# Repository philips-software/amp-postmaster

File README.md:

# Postmaster (Programmer Of ST Microcontrollers Attached to ST Experiment boaRds)

<!-- markdownlint-disable -->

<!-- markdownlint enable -->

## Overview

Postmaster is a device that clicks on top of an STM32 Nucleo-F767ZI board from ST Microelectronics, and through its Ethernet connector you can program the Nucleo and communicate with it.

In this way, Postmaster is usable in hardware-in-the-loop tests, where a test board is reachable through the internet. That test board can first be programmed with the correct firmware. For communicating with the test board, a client can connect to Postmaster via a websocket connection, and talk to the attached board either via a plain UART connection, or via an [ECHO](https://philips-software.github.io/amp-embedded-infra-lib/embedded_infrastructure_library/7.0.0/Echo.html) connection. This communication line is used to execute tests.

Test boards enabled by Postmaster are intended to be inherently scalable; Adding tests boards in a setup should be as simple as putting a Postmaster on top of it, configuring the Postmaster with a few labels describing the characteristics of that board, and connecting it to the internet. A locally installed proxy (also part of this archive) provides discoverability of all Postmasters in its vicinity, and routes incoming requests for boards with certain characteristics to any available board.

By providing a schematics and PCB layout, the Postmaster firmware, and various tools, this repository aims to provide a full suite of components tackling all aspects of connecting a hardware-in-the-loop test board to the cloud.

Requirements of Postmaster are documented [here](Documents/Requirements.md).

## Community

This project uses the [CODE_OF_CONDUCT](./CODE_OF_CONDUCT.md) to define expected conduct in our community. Instances of abusive, harassing, or otherwise unacceptable behavior may be reported by contacting a project [CODEOWNER](.github/CODEOWNERS)

## Changelog

See [CHANGELOG](./CHANGELOG.md) for more info on what's been changed.

## Build

The Postmaster binaries can be built by executing the following commands:

```shell
cmake --preset stm32f407
cmake --build --preset stm32f407-MinSizeRel
```

The postmaster.flex utility can be build by executing the following commands:

```shell
cmake --preset host
cmake --build --preset host-RelWithDebInfo
```

## Reporting vulnerabilities

If you find a vulnerability, please report it to us!
See [security](.github/SECURITY.md) for more information.

## Licenses

See [LICENSE](./LICENSE.md)

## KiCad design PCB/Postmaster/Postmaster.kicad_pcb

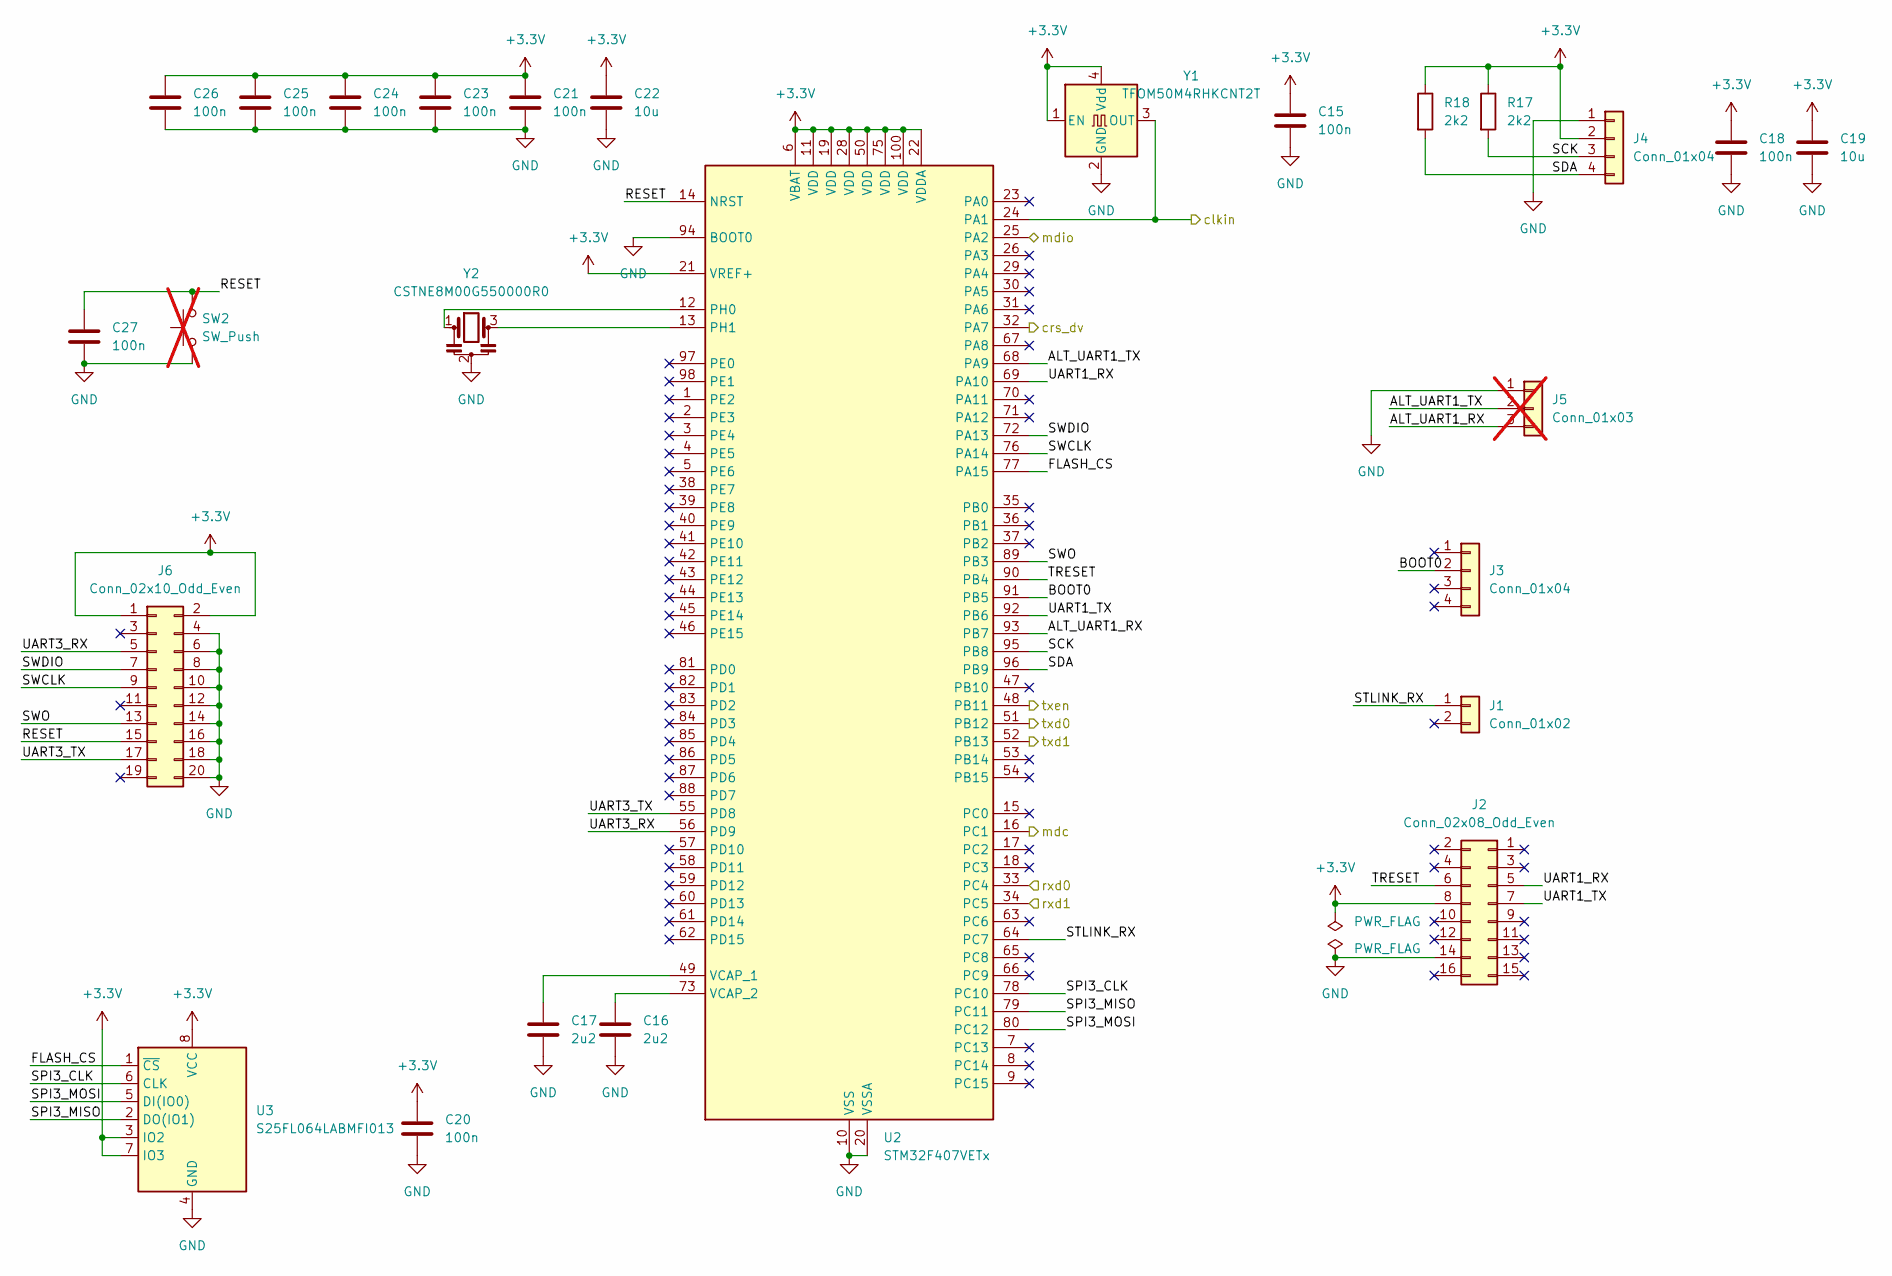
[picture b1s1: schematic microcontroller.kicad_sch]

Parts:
C15, C18, C20, C21, C23, C24, C25, C26, C27: 100n; C_0603_1608Metric; JLCPCBPart C14663
C16, C17: 2u2; C_0603_1608Metric; JLCPCBPart C23630
C19, C22: 10u; C_0603_1608Metric; JLCPCBPart C19702
J1: Conn_01x02; PinSocket_1x02_P2.54mm_Vertical; JLCPCBPart C7509512
J2: Conn_02x08_Odd_Even; PinHeader_2x08_P2.54mm_Vertical; JLCPCBPart C5383108
J3, J4: Conn_01x04; PinHeader_1x04_P2.54mm_Vertical; JLCPCBPart C7430360
J5: Conn_01x03; PinHeader_1x03_P2.54mm_Vertical; not fitted
J6: Conn_02x10_Odd_Even; IDC-Header_2x10_P2.54mm_Vertical; JLCPCBPart C3405
R17, R18: 2k2; R_0603_1608Metric; JLCPCBPart C4190
SW2: SW_Push; SW_SPST_TL3305B; not fitted
U2: STM32F407VETx; LQFP-100_14x14mm_P0.5mm; JLCPCBPart C28730
U3: S25FL064LABMFI013; SOIC-8_5.23x5.23mm_P1.27mm; JLCPCBPart C2951282
Y1: TFOM50M4RHKCNT2T; Oscillator_SMD_Abracon_ASE-4Pin_3.2x2.5mm; JLCPCBPart C454615
Y2: CSTNE8M00G550000R0; Resonator_SMD_Murata_CSTxExxV-3Pin_3.0x1.1mm; JLCPCBPart C341522

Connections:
+3.3V: C15.1, C18.1, C19.1, C20.1, C21.1, C22.1, C23.1, C24.1, C25.1, C26.1, J2.8, J4.2, J6.1, J6.2, R17.1, R18.1, U2.6 (VBAT), U2.11 (VDD), U2.19 (VDD), U2.21 (VREF+), U2.22 (VDDA), U2.28 (VDD), U2.50 (VDD), U2.75 (VDD), U2.100 (VDD), U3.3 (IO2), U3.7 (IO3), U3.8 (VCC), Y1.1 (EN), Y1.4 (Vdd); also elsewhere on the board
/Ethernet/clkin: U2.24 (PA1), Y1.3 (OUT); also elsewhere on the board
/Ethernet/crs_dv: U2.32 (PA7); also elsewhere on the board
/Ethernet/mdc: U2.16 (PC1); also elsewhere on the board
/Ethernet/mdio: U2.25 (PA2); also elsewhere on the board
/Ethernet/rxd0: U2.33 (PC4); also elsewhere on the board
/Ethernet/rxd1: U2.34 (PC5); also elsewhere on the board
/Ethernet/txd0: U2.51 (PB12); also elsewhere on the board
/Ethernet/txd1: U2.52 (PB13); also elsewhere on the board
/Ethernet/txen: U2.48 (PB11); also elsewhere on the board
/Microcontroller/ALT_UART1_RX: J5.3, U2.93 (PB7)
/Microcontroller/ALT_UART1_TX: J5.2, U2.68 (PA9)
/Microcontroller/BOOT0: J3.2, U2.91 (PB5)
/Microcontroller/FLASH_CS: U2.77 (PA15), U3.1 (~CS)
/Microcontroller/RESET: C27.1, J6.15, SW2.2, U2.14 (NRST)
/Microcontroller/SCK: J4.3, R17.2, U2.95 (PB8)
/Microcontroller/SDA: J4.4, R18.2, U2.96 (PB9)
/Microcontroller/SPI3_CLK: U2.78 (PC10), U3.6 (CLK)
/Microcontroller/SPI3_MISO: U2.79 (PC11), U3.2 (DO(IO1))
/Microcontroller/SPI3_MOSI: U2.80 (PC12), U3.5 (DI(IO0))
/Microcontroller/STLINK_RX: J1.1, U2.64 (PC7)
/Microcontroller/SWCLK: J6.9, U2.76 (PA14)
/Microcontroller/SWDIO: J6.7, U2.72 (PA13)
/Microcontroller/SWO: J6.13, U2.89 (PB3)
/Microcontroller/TRESET: J2.6, U2.90 (PB4)
/Microcontroller/UART1_RX: J2.5, U2.69 (PA10)
/Microcontroller/UART1_TX: J2.7, U2.92 (PB6)
/Microcontroller/UART3_RX: J6.5, U2.56 (PD9)
/Microcontroller/UART3_TX: J6.17, U2.55 (PD8)
GND: C15.2, C16.2, C17.2, C18.2, C19.2, C20.2, C21.2, C22.2, C23.2, C24.2, C25.2, C26.2, C27.2, J2.14, J4.1, J5.1, J6.4, J6.6, J6.8, J6.10, J6.12, J6.14, J6.16, J6.18, J6.20, SW2.1, U2.10 (VSS), U2.20 (VSSA), U2.27 (VSS), U2.74 (VSS), U2.94 (BOOT0), U2.99 (VSS), U3.4 (GND), Y1.2 (GND), Y2.2; also elsewhere on the board
unnamed: U2.12 (PH0), Y2.1
unnamed: U2.13 (PH1), Y2.3
unnamed: C17.1, U2.49 (VCAP_1)
unnamed: C16.1, U2.73 (VCAP_2)

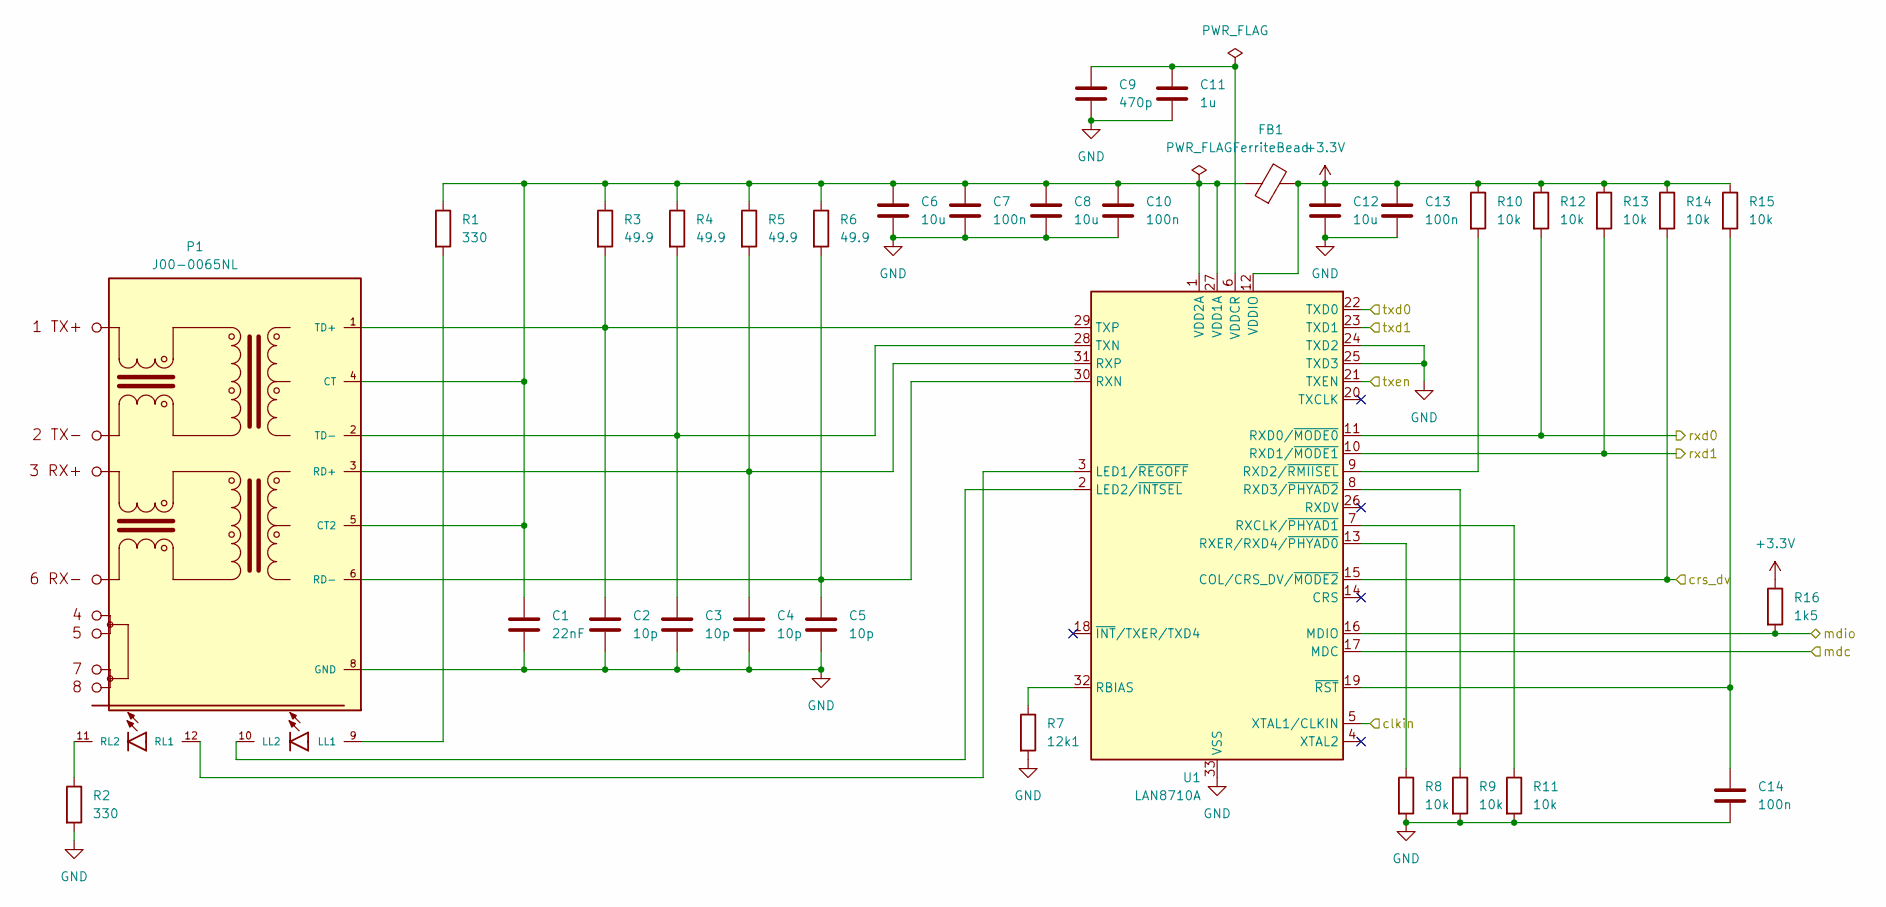
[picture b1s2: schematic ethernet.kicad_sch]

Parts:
C1: 22nF; C_0603_1608Metric; JLCPCBPart C21122
C2, C3, C4, C5: 10p; C_0603_1608Metric; JLCPCBPart C1634
C6, C8, C12: 10u; C_0603_1608Metric; JLCPCBPart C19702
C7, C10, C13, C14: 100n; C_0603_1608Metric; JLCPCBPart C14663
C9: 470p; C_0603_1608Metric; JLCPCBPart C1620
C11: 1u; C_0805_2012Metric; JLCPCBPart C15849
FB1: FerriteBead; L_0603_1608Metric; JLCPCBPart C1002
P1: J00-0065NL; PULSE_J00-0065NL; JLCPCBPart C3178480
R1, R2: 330; R_0603_1608Metric; JLCPCBPart C23138
R3, R4, R5, R6: 49.9; R_0603_1608Metric; JLCPCBPart C269902
R7: 12k1; R_0603_1608Metric; JLCPCBPart C22864
R8, R9, R10, R11, R12, R13, R14, R15: 10k; R_0603_1608Metric; JLCPCBPart C25804
R16: 1k5; R_0603_1608Metric; JLCPCBPart C22843
U1: LAN8710A; QFN-32-1EP_5x5mm_P0.5mm_EP3.3x3.3mm_ThermalVias; JLCPCBPart C46185

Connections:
+3.3V: C12.1, C13.1, FB1.2, R10.1, R12.1, R13.1, R14.1, R15.1, R16.1, U1.12 (VDDIO); also elsewhere on the board
/Ethernet/clkin: U1.5 (XTAL1/CLKIN); also elsewhere on the board
/Ethernet/crs_dv: R14.2, U1.15 (COL/CRS_DV/~MODE2); also elsewhere on the board
/Ethernet/mdc: U1.17 (MDC); also elsewhere on the board
/Ethernet/mdio: R16.2, U1.16 (MDIO); also elsewhere on the board
/Ethernet/rxd0: R12.2, U1.11 (RXD0/~MODE0); also elsewhere on the board
/Ethernet/rxd1: R13.2, U1.10 (RXD1/~MODE1); also elsewhere on the board
/Ethernet/txd0: U1.22 (TXD0); also elsewhere on the board
/Ethernet/txd1: U1.23 (TXD1); also elsewhere on the board
/Ethernet/txen: U1.21 (TXEN); also elsewhere on the board
GND: C1.2, C2.2, C3.2, C4.2, C5.2, C6.2, C7.2, C8.2, C9.2, C10.2, C11.2, C12.2, C13.2, C14.2, P1.8 (GND), R2.2, R7.2, R8.2, R9.2, R11.2, U1.24 (TXD2), U1.25 (TXD3), U1.33 (VSS); also elsewhere on the board
unnamed: C1.1, C6.1, C7.1, C8.1, C10.1, FB1.1, P1.4 (CT), P1.5 (CT2), R1.1, R3.1, R4.1, R5.1, R6.1, U1.1 (VDD2A), U1.27 (VDD1A)
unnamed: P1.9 (LL1), R1.2
unnamed: P1.10 (LL2), U1.2 (LED2/~INTSEL)
unnamed: C4.1, P1.3 (RD+), R5.2, U1.31 (RXP)
unnamed: C5.1, P1.6 (RD-), R6.2, U1.30 (RXN)
unnamed: P1.12 (RL1), U1.3 (LED1/~REGOFF)
unnamed: P1.11 (RL2), R2.1
unnamed: C2.1, P1.1 (TD+), R3.2, U1.29 (TXP)
unnamed: C3.1, P1.2 (TD-), R4.2, U1.28 (TXN)
unnamed: R7.1, U1.32 (RBIAS)
unnamed: R11.1, U1.7 (RXCLK/~PHYAD1)
unnamed: R10.2, U1.9 (RXD2/~RMIISEL)
unnamed: R9.1, U1.8 (RXD3/~PHYAD2)
unnamed: R8.1, U1.13 (RXER/RXD4/~PHYAD0)
unnamed: C9.1, C11.1, U1.6 (VDDCR)
unnamed: C14.1, R15.2, U1.19 (~RST)

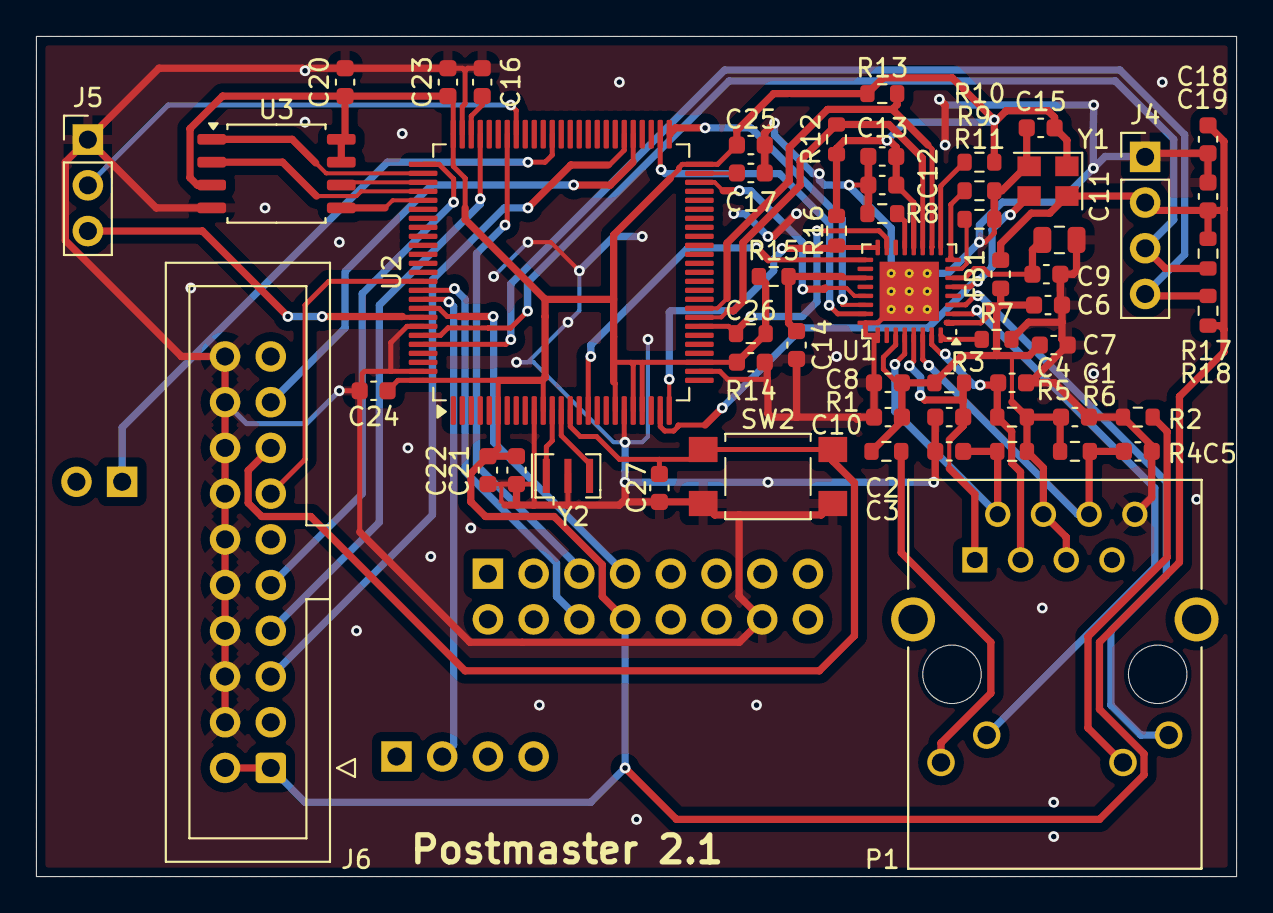
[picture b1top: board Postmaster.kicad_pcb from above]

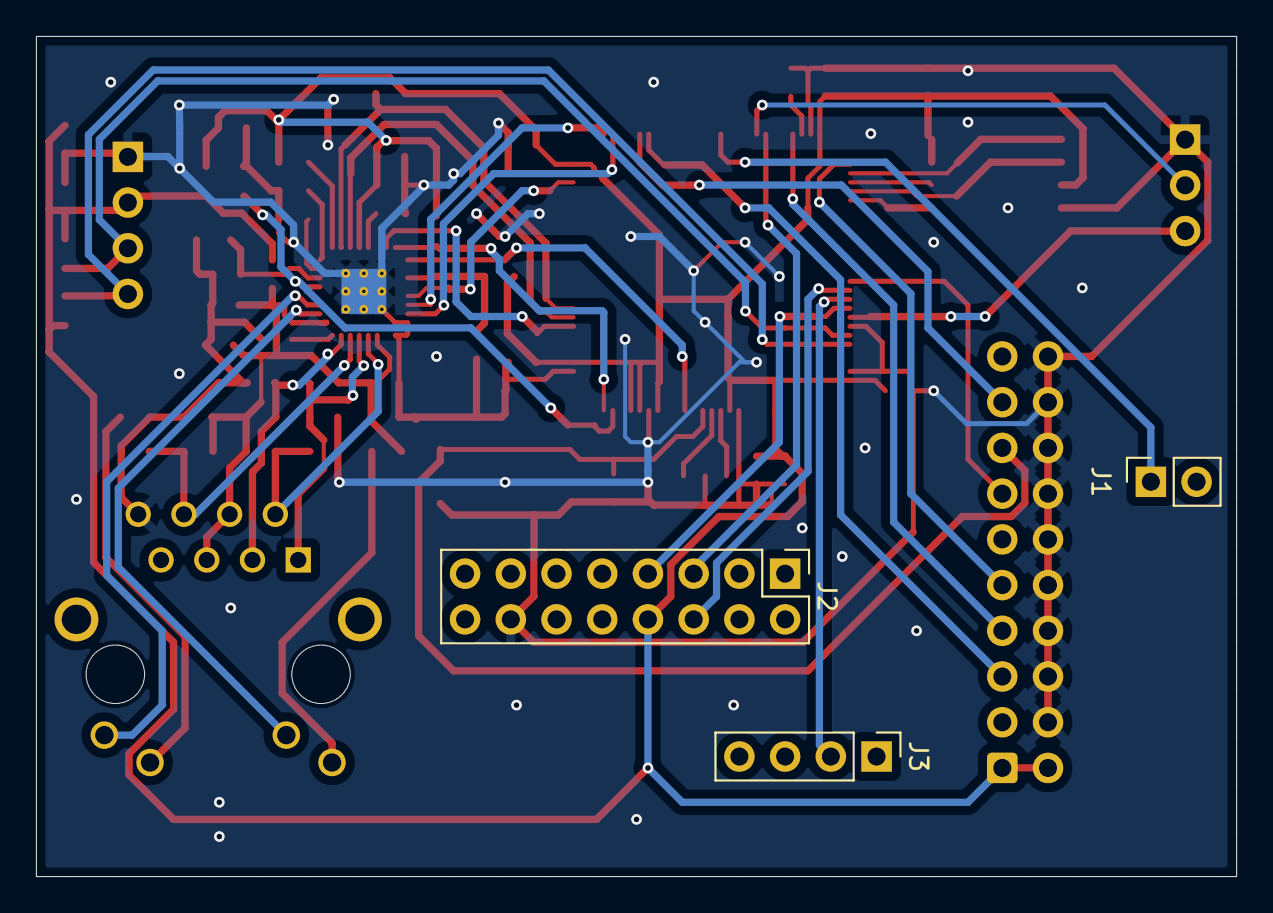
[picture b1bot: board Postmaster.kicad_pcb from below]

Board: 2 copper layers, 66.7 x 46.7 mm, 59 parts (3 on the bottom side), 50 nets.

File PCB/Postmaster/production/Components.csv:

Comment,Designator,Footprint,JLCPCBPart
22nF,C1,Capacitor_SMD:C_0603_1608Metric,C21122
10p,"C2,C3,C4,C5",Capacitor_SMD:C_0603_1608Metric,C1634
10u,"C6,C8,C12,C19,C22",Capacitor_SMD:C_0603_1608Metric,C19702
100n,"C7,C10,C13,C14,C15,C18,C20,C21,C23,C24,C25,C26,C27",Capacitor_SMD:C_0603_1608Metric,C14663
470p,C9,Capacitor_SMD:C_0603_1608Metric,C1620
1u,C11,Capacitor_SMD:C_0805_2012Metric,C15849
2u2,"C16,C17",Capacitor_SMD:C_0603_1608Metric,C23630
FerriteBead,FB1,Inductor_SMD:L_0603_1608Metric,C1002
Conn_01x02,J1,Connector_PinSocket_2.54mm:PinSocket_1x02_P2.54mm_Vertical,C7509512
Conn_02x08_Odd_Even,J2,Connector_PinHeader_2.54mm:PinHeader_2x08_P2.54mm_Vertical,C5383108
Conn_01x04,"J3,J4",Connector_PinHeader_2.54mm:PinHeader_1x04_P2.54mm_Vertical,C7430360
Conn_01x03,J5,Connector_PinHeader_2.54mm:PinHeader_1x03_P2.54mm_Vertical,
Conn_02x10_Odd_Even,J6,Connector_IDC:IDC-Header_2x10_P2.54mm_Vertical,C3405
J00-0065NL,P1,PostmasterParts:PULSE_J00-0065NL,C3178480
330,"R1,R2",Resistor_SMD:R_0603_1608Metric,C23138
49.9,"R3,R4,R5,R6",Resistor_SMD:R_0603_1608Metric,C269902
12k1,R7,Resistor_SMD:R_0603_1608Metric,C22864
10k,"R8,R9,R10,R11,R12,R13,R14,R15",Resistor_SMD:R_0603_1608Metric,C25804
1k5,R16,Resistor_SMD:R_0603_1608Metric,C22843
2k2,"R17,R18",Resistor_SMD:R_0603_1608Metric,C4190
SW_Push,SW2,Button_Switch_SMD:SW_SPST_TL3305B,
LAN8710A,U1,Package_DFN_QFN:QFN-32-1EP_5x5mm_P0.5mm_EP3.3x3.3mm_ThermalVias,C46185
STM32F407VETx,U2,Package_QFP:LQFP-100_14x14mm_P0.5mm,C28730
S25FL064LABMFI013,U3,Package_SO:SOIC-8_5.23x5.23mm_P1.27mm,C2951282
TFOM50M4RHKCNT2T,Y1,Oscillator:Oscillator_SMD_Abracon_ASE-4Pin_3.2x2.5mm,C454615
CSTNE8M00G550000R0,Y2,Crystal:Resonator_SMD_Murata_CSTxExxV-3Pin_3.0x1.1mm,C341522

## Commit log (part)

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2024-12-04 Update submodules
2024-12-04 ci: validate pull request titles
2024-12-06 feat(deps): bump the git-submodules group with 2 updates
    Bumps the git-submodules group with 2 updates: [amp-embedded-infra-lib](https://github.com/philips-software/amp-embedded-infra-lib) and [amp-hal-st](https://github.com/philips-software/amp-hal-st).
    Updates `amp-embedded-infra-lib` from `6c84af5` to `c77731b`
    - [Release notes](https://github.com/philips-software/amp-embedded-infra-lib/releases)
    - [Commits](https://github.com/philips-software/amp-embedded-infra-lib/compare/6c84af5324c79219059d1066cc5ce3aad8f2b927...c77731ba79bfbe8af22450cf33fcdf4fd30a3587)
    Updates `amp-hal-st` from `1529067` to `f11d3bf`
    - [Release notes](https://github.com/philips-software/amp-hal-st/releases)
2024-12-19 postmaster/flex/Main: Fix reading from environment
2025-01-10 feat(deps): bump the git-submodules group across 1 directory with 3 updates
    Bumps the git-submodules group with 3 updates in the / directory: [amp-embedded-infra-lib](https://github.com/philips-software/amp-embedded-infra-lib), [amp-hal-st](https://github.com/philips-softwar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
    Updates `amp-embedded-infra-lib` from `6c84af5` to `ae01eea`
    - [Release notes](https://github.com/philips-software/amp-embedded-infra-lib/releases)
    - [Commits](https://github.com/philips-software/amp-embedded-infra-lib/compare/6c84af5324c79219059d1066cc5ce3aad8f2b927...ae01eeae459647a0f8a52430bb26740d47b2945e)
    Updates `amp-hal-st` from `1
2025-01-19 Accept multiple connections on port 80, one connection on port 8080
2025-01-31 build(deps): bump the github-actions group across 1 directory with 6 updates
    Bumps the github-actions group with 6 updates in the / directory:
    | Package | From | To |
    | --- | --- | --- |
    | [hendrikmuhs/ccache-action](https://github.com/hendrikmuhs/ccache-action) | `1.2.14` | `1.2.16` |
    | [oxsecurity/megalinter](https://github.com/oxsecurity/megalinter) | `8.3.0` | `8.4.1` |
    | [actions/upload-artifact](https://github.com/actions/upload-artifact) | `4.5.0` | `4.6.0` |
2025-02-13 build(deps): bump philips-software/amp-devcontainer-cpp
    Bumps [philips-software/amp-devcontainer-cpp](https://github.com/philips-software/amp-devcontainer) from v5.6.0 to v5.6.1.
    - [Release notes](https://github.com/philips-software/amp-devcontainer/releases)
    - [Changelog](https://github.com/philips-software/amp-devcontainer/blob/main/CHANGELOG.md)
    - [Commits](https://github.com/philips-software/amp-devcontainer/compare/v5.6.0...v5.6.1)
    ---
    updated-dependencies:
2025-02-20 feat: add kicad design for Postmaster (#51)
    * feat: redo the schematics and board in KiCad
    * Update schematics
    * Update schematics
    * Update schematics
    * Update schematics
    * Update schematics, add production files
2025-03-03 feat(deps): bump the git-submodules group across 1 directory with 3 updates
    Bumps the git-submodules group with 3 updates in the / directory: [amp-embedded-infra-lib](https://github.com/philips-software/amp-embedded-infra-lib), [amp-hal-st](https://github.com/philips-softwar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
    Updates `amp-embedded-infra-lib` from `6c84af5` to `eccbab6`
    - [Release notes](https://github.com/philips-software/amp-embedded-infra-lib/releases)
    - [Commits](https://github.com/philips-software/amp-embedded-infra-lib/compare/6c84af5324c79219059d1066cc5ce3aad8f2b927...eccbab6e47da83929395a27b047a695ecd29e7a6)
    Updates `amp-hal-st` from `1
2025-03-24 build(deps): bump the github-actions group across 1 directory with 6 updates
    Bumps the github-actions group with 6 updates in the / directory:
    | Package | From | To |
    | --- | --- | --- |
    | [actions/cache](https://github.com/actions/cache) | `4.2.1` | `4.2.3` |
    | [oxsecurity/megalinter](https://github.com/oxsecurity/megalinter) | `8.4.2` | `8.5.0` |
    | [actions/upload-artifact](https://github.com/actions/upload-artifact) | `4.6.0` | `4.6.2` |
2025-04-25 build(deps): bump philips-software/amp-devcontainer-cpp
    Bumps [philips-software/amp-devcontainer-cpp](https://github.com/philips-software/amp-devcontainer) from v5.6.2 to v6.0.1.
    - [Release notes](https://github.com/philips-software/amp-devcontainer/releases)
    - [Changelog](https://github.com/philips-software/amp-devcontainer/blob/main/CHANGELOG.md)
    - [Commits](https://github.com/philips-software/amp-devcontainer/compare/v5.6.2...v6.0.1)
    ---
    updated-dependencies:
2025-05-08 build(deps): bump oxsecurity/megalinter in the github-actions group (#78)
    Bumps the github-actions group with 1 update: [oxsecurity/megalinter](https://github.com/oxsecurity/megalinter).
    Updates `oxsecurity/megalinter` from 8.6.0 to 8.7.0
    - [Release notes](https://github.com/oxsecurity/megalinter/releases)
    - [Changelog](https://github.com/oxsecurity/megalinter/blob/main/CHANGELOG.md)
    - [Commits](https://github.com/oxsecurity/megalinter/compare/04cf22b980c2e9c2121553417ed651c944afc8e1...5a91fb06c83d0e69fbd23756d47438aa723b4a5a)
    ---
2025-05-21 chore(deps): bump philips-software/amp-devcontainer-cpp
    Bumps [philips-software/amp-devcontainer-cpp](https://github.com/philips-software/amp-devcontainer) from v6.0.1 to v6.0.2.
    - [Release notes](https://github.com/philips-software/amp-devcontainer/releases)
    - [Changelog](https://github.com/philips-software/amp-devcontainer/blob/main/CHANGELOG.md)
    - [Commits](https://github.com/philips-software/amp-devcontainer/compare/v6.0.1...v6.0.2)
    ---
    updated-dependencies:
2025-05-22 fix: align flash writes to 16 bytes (#80)
    * fix: align flash writes to 16 bytes
    * Wait for flash initialization done
    * FlexHttpClient: Move attaching of websocket
    * FirmwareReceptorResetTarget: Use timers instead of HAL_Delay
    * Set starting
    * Update container
2025-06-16 chore(deps): bump the github-actions group across 1 directory with 6 updates
    Bumps the github-actions group with 6 updates in the / directory:
    | Package | From | To |
    | --- | --- | --- |
    | [actions/checkout](https://github.com/actions/checkout) | `4.1.7` | `4.2.2` |
    | [docker/metadata-action](https://github.com/docker/metadata-action) | `5.5.1` | `5.7.0` |
    | [docker/setup-buildx-action](https://github.com/docker/setup-buildx-action) | `3.6.1` | `3.10.0` |
2025-08-08 chore(deps): bump the github-actions group across 1 directory with 4 updates (#98)
    Bumps the github-actions group with 4 updates in the / directory: [actions/cache](https://github.com/actions/cache), [docker/metadata-action](https://github.com/docker/metadata-action), [docker/login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
    Updates `actions/cache` from 4.2.3 to 4.2.4
    - [Release notes](https://github.com/actions/cache/releases)
    - [Changelog](https://github.com/actions/cache/blob/main/RELEASES.md)
    - [Commits](https://github.com/actions/cache/compare/5a3ec84eff668545956fd18022155c47e9
2025-09-10 chore(deps): bump philips-software/amp-devcontainer-cpp
    Bumps [philips-software/amp-devcontainer-cpp](https://github.com/philips-software/amp-devcontainer) from 6.2.1 to 6.3.0.
    - [Release notes](https://github.com/philips-software/amp-devcontainer/releases)
    - [Changelog](https://github.com/philips-software/amp-devcontainer/blob/main/CHANGELOG.md)
    - [Commits](https://github.com/philips-software/amp-devcontainer/compare/v6.2.1...v6.3.0)
    ---
    updated-dependencies:
2025-10-08 chore(deps): bump philips-software/amp-devcontainer-cpp (#114)
    Bumps [philips-software/amp-devcontainer-cpp](https://github.com/philips-software/amp-devcontainer) from 6.2.1 to v6.5.0.
    - [Release notes](https://github.com/philips-software/amp-devcontainer/releases)
    - [Changelog](https://github.com/philips-software/amp-devcontainer/blob/main/CHANGELOG.md)
    - [Commits](https://github.com/philips-software/amp-devcontainer/compare/v6.2.1...v6.5.0)
    ---
    updated-dependencies:
2025-10-23 chore: enable usb passthrough debugging (#119)
2025-10-27 feat(deps): bump the git-submodules group across 1 directory with 3 updates
    Bumps the git-submodules group with 3 updates in the / directory: [amp-embedded-infra-lib](https://github.com/philips-software/amp-embedded-infra-lib), [amp-hal-st](https://github.com/philips-softwar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
    Updates `amp-embedded-infra-lib` from `9d3718f` to `2c26042`
    - [Release notes](https://github.com/philips-software/amp-embedded-infra-lib/releases)
    - [Commits](https://github.com/philips-software/amp-embedded-infra-lib/compare/9d3718fe966a1b4308b1f7ee4deb572958733cf9...2c260424bb9e220a8ccc9a4ea43ec7154cfd2eb0)
    Updates `amp-hal-st` from `f
2025-11-26 chore(deps): bump philips-software/amp-devcontainer-cpp
    Bumps [philips-software/amp-devcontainer-cpp](https://github.com/philips-software/amp-devcontainer) from v6.5.0 to v6.6.1.
    - [Release notes](https://github.com/philips-software/amp-devcontainer/releases)
    - [Changelog](https://github.com/philips-software/amp-devcontainer/blob/main/CHANGELOG.md)
    - [Commits](https://github.com/philips-software/amp-devcontainer/compare/v6.5.0...v6.6.1)
    ---
    updated-dependencies:
2025-12-16 build: remove MinSizeRel configuration
2025-12-18 Allow containers in linting
2025-12-19 Create installation package
2025-12-19 chore(main): release 0.3.0
2025-12-22 build(deps): bump actions/download-artifact from 6.0.0 to 7.0.0
    Bumps [actions/download-artifact](https://github.com/actions/download-artifact) from 6.0.0 to 7.0.0.
    - [Release notes](https://github.com/actions/download-artifact/releases)
    - [Commits](https://github.com/actions/download-artifact/compare/018cc2cf5baa6db3ef3c5f8a56943fffe632ef53...37930b1c2abaa49bbe596cd826c3c89aef350131)
    ---
    updated-dependencies:
    - dependency-name: actions/download-artifact
2026-01-05 feat(deps): bump the git-submodules group across 1 directory with 3 updates (#153)
    Bumps the git-submodules group with 3 updates in the / directory: [amp-embedded-infra-lib](https://github.com/philips-software/amp-embedded-infra-lib), [amp-hal-st](https://github.com/philips-softwar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
    Updates `amp-embedded-infra-lib` from `7b3044e` to `eda0964`
    - [Release notes](https://github.com/philips-software/amp-embedded-infra-lib/releases)
    - [Commits](https://github.com/philips-software/amp-embedded-infra-lib/compare/7b3044eedcc65598b3f6df89f204d9a69895df39...eda09647446baea1a96017675e09e654c23bee9d)
    Updates `amp-hal-st`
2026-01-05 fix: install postmaster binaries (#146)
    * fix: install postmaster binaries
    * Add map and hex files
    * Create and release upgrade pack
    * Fix character
    * Move Build Upgrade Pack to continuous-integration.yml
    * Fix artifact name
2026-01-06 fix: release version in upg file names
2026-01-06 Fix sed formatting
2026-01-07 Moar quotes
2026-01-08 build(deps): bump docker/setup-buildx-action in the github-actions group
    Bumps the github-actions group with 1 update: [docker/setup-buildx-action](https://github.com/docker/setup-buildx-action).
    Updates `docker/setup-buildx-action` from 3.11.1 to 3.12.0
    - [Release notes](https://github.com/docker/setup-buildx-action/releases)
    - [Commits](https://github.com/docker/setup-buildx-action/compare/e468171a9de216ec08956ac3ada2f0791b6bd435...8d2750c68a42422c14e847fe6c8ac0403b4cbd6f)
    ---
    updated-dependencies:
2026-01-08 Refactor
2026-01-08 chore(main): release 0.5.0 (#166)
2026-02-05 build(deps): bump the github-actions group across 1 directory with 4 updates
    Bumps the github-actions group with 4 updates in the / directory: [step-security/harden-runner](https://github.com/step-security/harden-runner), [docker/login-action](https://github.com/docker/login-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
    Updates `step-security/harden-runner` from 2.14.0 to 2.14.1
    - [Release notes](https://github.com/step-security/harden-runner/releases)
    - [Commits](https://github.com/step-security/harden-runner/compare/20cf305ff2072d973412fa9b1e3a4f227bda3c76...e3f713f2d8f53843e71c69a996d56f51aa9adfb9)
2026-03-06 build(deps): bump the github-actions group across 1 directory with 3 updates
    Bumps the github-actions group with 3 updates in the / directory: [actions/checkout](https://github.com/actions/checkout), [zizmorcore/zizmor-action](https://github.com/zizmorcore/zizmor-action) and 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
    Updates `actions/checkout` from 6.0.1 to 6.0.2
    - [Release notes](https://github.com/actions/checkout/releases)
    - [Changelog](https://github.com/actions/checkout/blob/main/CHANGELOG.md)
    - [Commits](https://github.com/actions/checkout/compare/8e8c483db84b4bee98b60c0593521ed34d9990e8...de0fac2e4500dabe0009e67214ff5f5447ce83dd)
    Updates `zizmorcore/zizmor-action` from 0.3.
